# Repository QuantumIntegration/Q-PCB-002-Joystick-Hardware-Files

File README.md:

# Quantum DIY Kit Hardware Files - Joystick
## Introduction

This repository contains all the hardware files necessary to build the PCBs and assemble the DIY kits. The PCBs can be ordered from for example [JLCPCB](https://jlcpcb.com/) or [PCBWay](https://www.pcbway.com/). The components can be sourced mostly from [Amazon](https://amazon.com/) or [Digikey](https://digikey.com/), according to the links in the BOM file.

## Download the correct revision

If you are nor familiar with the git version control system, please follow these simple steps to download your version of the DIY kit

<em>1. Click the branch button</em>

<em>2. Select the branch matching your revision</em>

<em>3. Click the Code button</em>

<em>4. Download the ZIP and extract it on your machine</em>

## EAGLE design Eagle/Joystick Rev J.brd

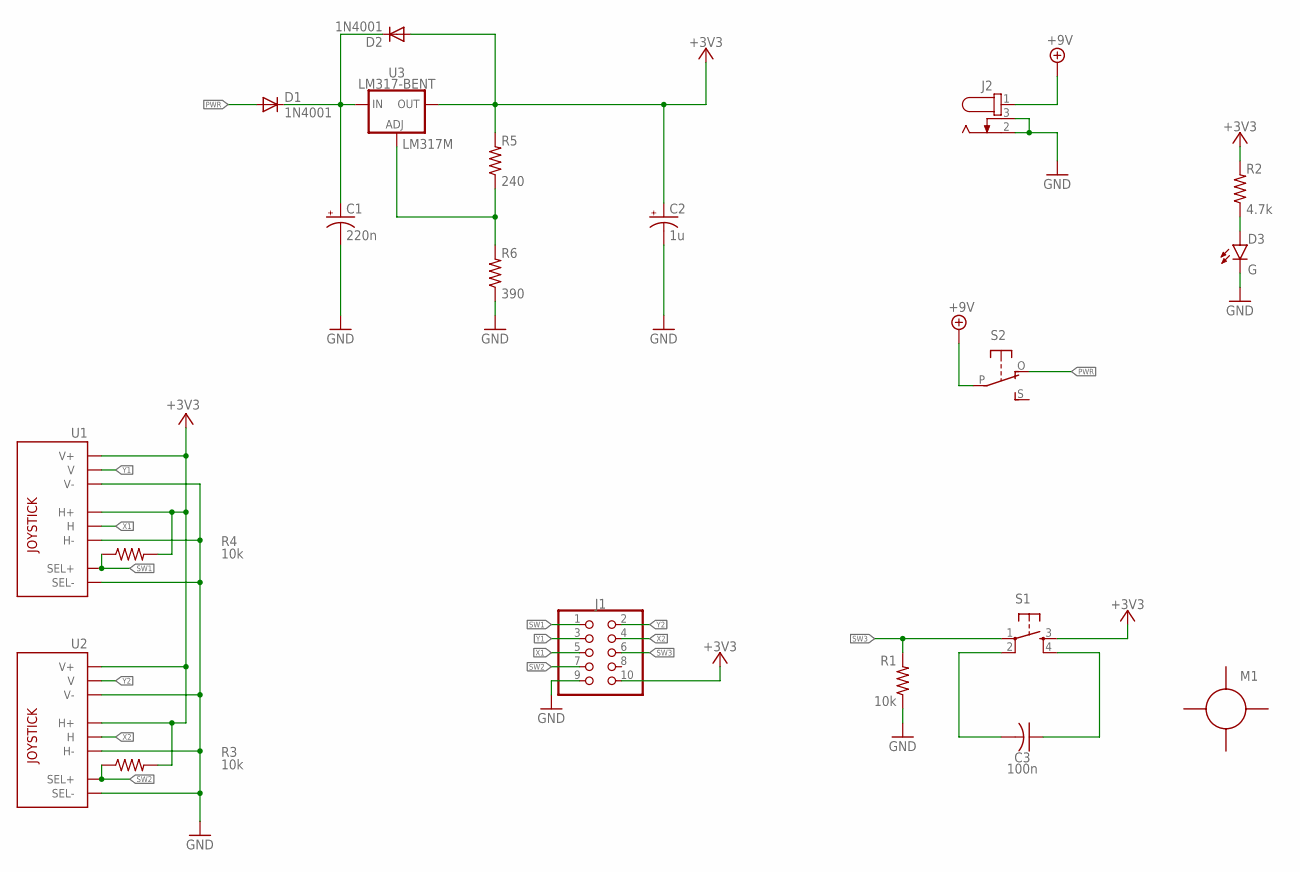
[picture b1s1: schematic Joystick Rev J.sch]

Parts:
C1: 220n; E2-4
C2: 1u; E2-4
C3: 100n; C050-024X044
D1, D2: 1N4001; DO41-10
D3: G; LED5MM
J1: RIBBON-2X5; 057-010-1
J2: 694106301002
M1: 9V-HOLDERM2.5; 9V-HOLDER-M2.5
R1, R3, R4: 10k; 0207/10
R2: 4.7k; 0207/10
R5: 240; 0207/10
R6: 390; 0207/10
S1: TACTILE-BUTTON40XX; B3F-40XX
S2: SLIDE-SWITCHSIDE; EG1270-90
U1, U2: JOYSTICK
U3: LM317-BENT; T03B; PARTNUMBER LM317M

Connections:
+3V3: C2.+, D2.A, J1.10, R2.2, R3.2, R4.2, R5.2, S1.3 (S), U1.H1 (H+), U1.V1 (V+), U2.H1 (H+), U2.V1 (V+), U3.2 (OUT)
+9V: J2.1, S2.P
GND: C1.-, C2.-, D3.K (C), J1.9, J2.2, J2.3, R1.1, R6.1, U1.B2A (SEL-), U1.H3 (H-), U1.V3 (V-), U2.B2A (SEL-), U2.H3 (H-), U2.V3 (V-)
unnamed: R5.1, R6.2, U3.1 (ADJ)
unnamed: D3.A, R2.1
unnamed: C3.1, S1.4 (S1)
unnamed: C3.2, S1.2 (P1)
unnamed: C1.+, D1.C, D2.C, U3.3 (IN)
PWR: D1.A, S2.O
SW1: J1.1, R4.1, U1.B1A (SEL+)
SW2: J1.7, R3.1, U2.B1A (SEL+)
SW3: J1.6, R1.2, S1.1
X1: J1.5, U1.H2 (H)
X2: J1.4, U2.H2 (H)
Y1: J1.3, U1.V2 (V)
Y2: J1.2, U2.V2 (V)

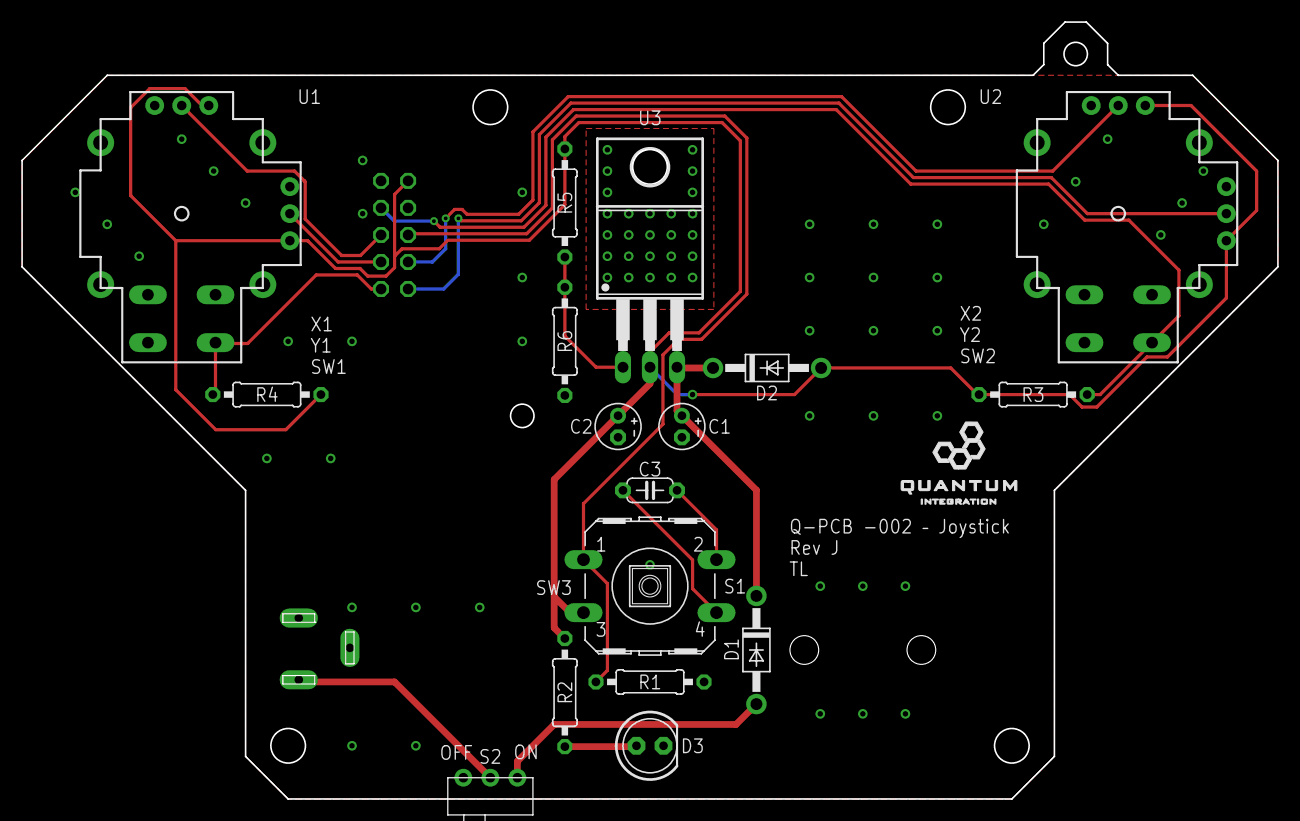
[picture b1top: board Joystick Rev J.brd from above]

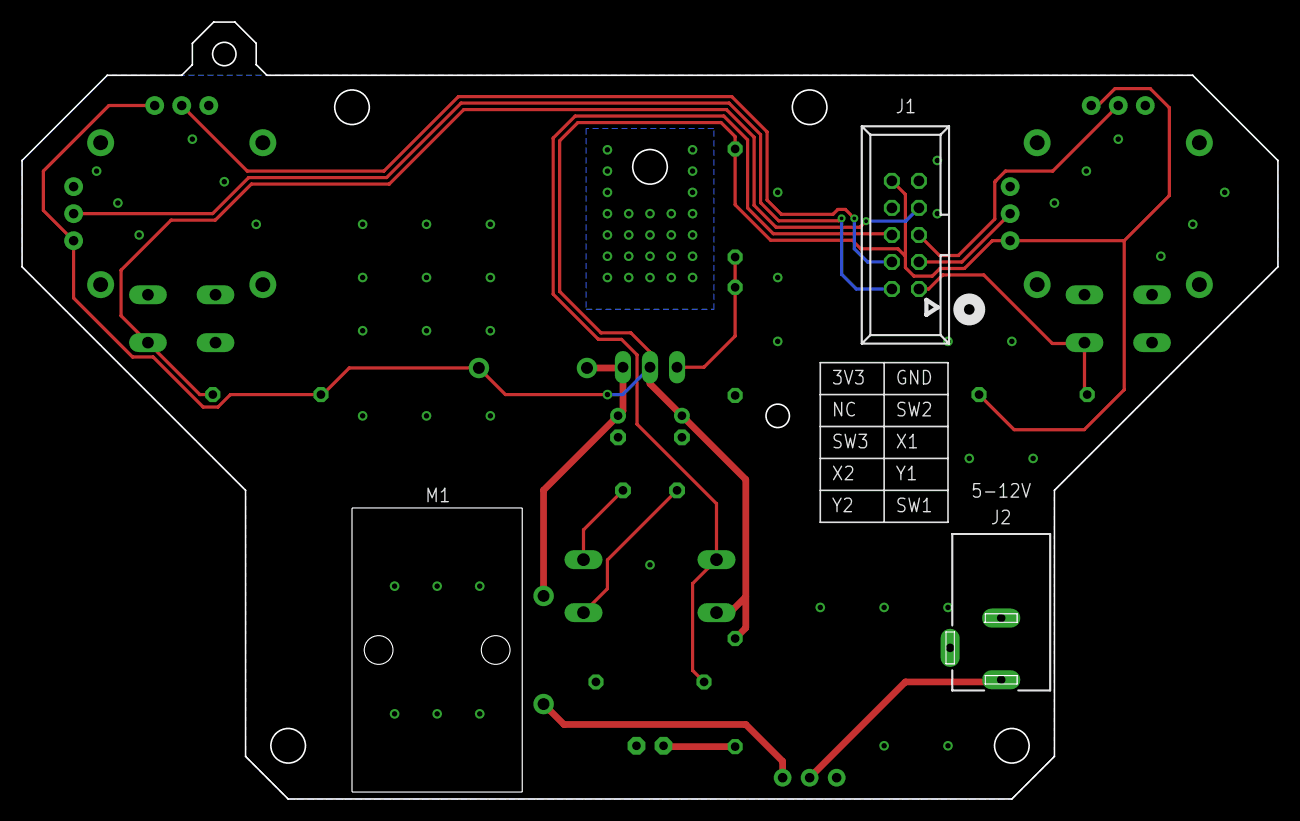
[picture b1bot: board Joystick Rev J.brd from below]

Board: 2 copper layers, 118.0 x 73.0 mm, 20 parts (3 on the bottom side), 16 nets.

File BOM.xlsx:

Index | Part | Value | Quantity | Designators | Package | Comments | Specific Part Reference | Part Link Example
1 | Joystick |  | 2 | U1, U2 |  | Large Button Spacing |  | https://www.digikey.com/product-detail/en/sparkfun-electroni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
2 | Barrell Jack |  | 1 | J2 |  | 2.1mm jack |  | https://www.digikey.com/products/en?keywords=694106301002
3 | Battery Holder |  | 1 | M1 |  | horizontal M3 holes |  | https://www.digikey.com/product-detail/en/keystone-electroni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
4 | Ribbon Connector |  | 1 | J1 |  | 2x5, keyed, male |  | https://www.digikey.com/product-detail/en/on-shore-technolog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
5 | Slide Switch |  | 1 | S2 |  | 90 degree | EG1270 | https://www.digikey.com/product-detail/en/e-switch/EG1270/EG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
6 | Tactile Button |  | 1 | S1 | B3F-40xx | black round color cap | Omron B3F-4055, Black round Cap | https://www.digikey.com/product-detail/en/omron-electronics-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
7 | Electrolytic Capacitor | 220n | 1 | C1 | E2-4 | H: 8mm, 50V |  | https://www.digikey.com/product-detail/en/nichicon/USP1H0R1M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
8 | Ceramic Capacitor | 100n | 1 | C3 | 024x044 |  |  | https://www.digikey.com/product-detail/en/kemet/C315C104M5U5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
9 | Diode | 1N4001 | 2 | D1, D2 |  |  |  | https://www.digikey.com/product-detail/en/comchip-technology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
10 | Electrolytic Capacitor | 1u | 1 | C2 | E2-4 | H: 8mm, 50V |  | https://www.digikey.com/product-detail/en/nichicon/USA1H010M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
11 | Resistor | 240 | 1 | R5 | 0207/10 | 1/4 W |  | https://www.amazon.com/SIQUK-Resistors-Resistor-Assortment-E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
12 | Resistor | 390 | 1 | R6 | 0207/10 | 1/4 W |  | https://www.amazon.com/SIQUK-Resistors-Resistor-Assortment-E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
13 | Resistor | 4.7k | 1 | R2 | 0207/10 | 1/4 W |  | https://www.amazon.com/SIQUK-Resistors-Resistor-Assortment-E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
14 | LED | green-diffused | 1 | D3 | 5mm |  |  | https://www.amazon.com/Diffused-Lighting-Electronics-Compone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
15 | LM317 |  | 1 | U3 | TO-220-3 |  | LM317T | https://www.digikey.com/product-detail/en/stmicroelectronics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
16 | Resistor | 10k | 3 | R1, R3, R4 | 0207/10 | 1/4 W |  | https://www.amazon.com/SIQUK-Resistors-Resistor-Assortment-E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
17 | Battery Harness |  | 1 |  |  | 2.1 mm plug |  | https://www.amazon.com/AKOAK-Battery-Button-Connector-Holder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
18 | M2 Standoff |  | 2 |  |  | 15mm, Female-Female |  | https://www.amazon.com/gp/product/B07CNF3W7B/ref=ppx_yo_dt_b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
19 | M2 Screw |  | 4 |  |  | 5mm |  | https://www.amazon.com/gp/product/B07CNF3W7B/ref=ppx_yo_dt_b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
20 | M2.5 Screw |  | 2 |  |  | 6mm |  | https://www.amazon.com/gp/product/B075K3QBMX/ref=ppx_yo_dt_b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
21 | M2.5 Nut |  | 2 |  |  |  |  | https://www.amazon.com/gp/product/B075K3QBMX/ref=ppx_yo_dt_b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
22 | M3 Screw |  | 5 |  |  | 6mm |  | https://www.amazon.com/gp/product/B07CNF3W7B/ref=ppx_yo_dt_b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
23 | M3 Nut |  | 1 |  |  |  |  | https://www.amazon.com/gp/product/B07CNF3W7B/ref=ppx_yo_dt_b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
24 | RIbbon Cable |  | 1 |  |  | rainbow colored |  | https://www.amazon.com/uxcell-Rainbow-Ribbon-Connector-19-7i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
25 | Ribbon End Piece |  | 1 |  |  | keyed |  | https://www.amazon.com/uxcell-Rainbow-Ribbon-Connector-19-7i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
26 | M4 Screw |  | 2 |  |  | 8mm |  | https://www.amazon.com/gp/product/B07CNF3W7B/ref=ppx_yo_dt_b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
27 | Thermal Pad with fitting |  | 1 |  |  | fits LM317 |  | https://www.digikey.com/product-detail/en/bergquist/HF115AC-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

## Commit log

2021-03-16 edited readme and gitignore
2021-03-16 added project content
2021-03-16 edited readme title
2021-03-16 added readme preview
2021-04-26 changes to BOM for manufacturing
2021-05-17 added Arduino files
2021-08-17 added schematic as PDF

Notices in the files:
parts and their libraries:
Wurth_Connectors_WR-DC: Copyright: Würth Elektronik
